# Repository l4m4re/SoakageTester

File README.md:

# SoakageTester
Hard and software for studying dielectric absorption aka "soakage" in electrolytic capacitors and/or batteries

# Intro

This is a capacitor/battery pulsed charge-discharge cycle tester, as part of a
project to investigate the theory that the well known "capacitor soakage" or
"battery action" effect observed with electrolytic capacitors can be enhanced
using pulsed charging, as demonstrated by John Bedini et al for years. For
more information on the theory, see my article about [The Cole-Hackenberger
(Gray) Power
Supply](http://www.tuks.nl/wiki/index.php/Main/ColeHackenbergerPowerSupply).

# Hardware

The hardware consists of:

1) An adjustable power supply, 0-300V;
2) Pulse charge circuitry, steered by a BeagleBone, using a MOSFET;
3) Current measurement circuitry, using a shunt, some opamps to amplify
the input signal, implement a low pass filter, etc.
4) Voltage measurement circuitry.

Both the current en voltage measurements are done by the BeagleBone using
it's analog inputs and it's ADC. 

Based on [small-scope](https://hackaday.io/project/5881-small-scope) by Marvin Sinister.

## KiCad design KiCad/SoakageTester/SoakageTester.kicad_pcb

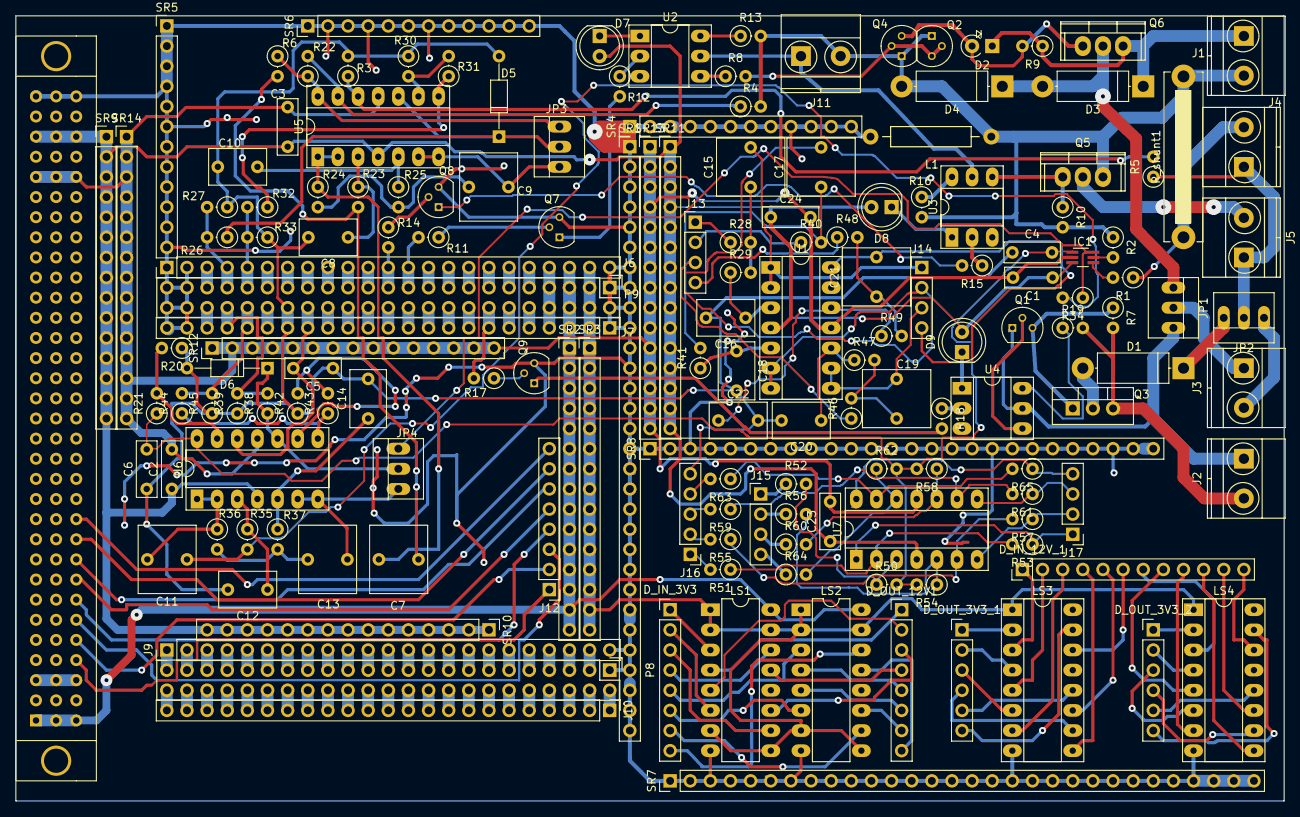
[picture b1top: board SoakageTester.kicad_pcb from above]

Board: 2 copper layers, 160.0 x 99.1 mm, 163 parts (0 on the bottom side), 230 nets.

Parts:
C1, C2, C3, C4, C5, C6, C23, C24: 100n; C_Rect_L7.0mm_W2.5mm_P5.00mm
C7, C9, C11, C13, C15, C17, C19, C21: 10n; C_Rect_L7.2mm_W8.5mm_P5.00mm_FKP2_FKP2_MKS2_MKP2
C8, C10, C12, C14, C16, C18, C20, C22: 1n; C_Rect_L7.2mm_W4.5mm_P5.00mm_FKS2_FKP2_MKS2_MKP2
D1, D3, D4: 1N4007; D_5W_P12.70mm_Horizontal
D2: 12V; D_A-405_P2.54mm_Vertical_KathodeUp
D5, D6: 1n4148; D_DO-35_SOD27_P10.16mm_Horizontal
D7, D8, D9: LED; LED_D5.0mm
D_IN_3V3: CONN_01X08; Pin_Header_Straight_1x08_Pitch2.54mm
D_IN_12V_1: CONN_01X12; Pin_Header_Straight_1x12_Pitch2.54mm
D_OUT_3V3_1, D_OUT_3V3_2: CONN_01X06; Pin_Header_Straight_1x06_Pitch2.54mm
D_OUT_12V1: CONN_01X08; Pin_Header_Straight_1x08_Pitch2.54mm
IC1: ina213; SOT-363_SC-70-6_Handsoldering
J1: 30-300V; TerminalBlock_Pheonix_MKDS1.5-2pol
J2: 12V_Bedini; TerminalBlock_Pheonix_MKDS1.5-2pol
J3: Coil; TerminalBlock_Pheonix_MKDS1.5-2pol
J4: Test Cap; TerminalBlock_Pheonix_MKDS1.5-2pol
J5: Load; TerminalBlock_Pheonix_MKDS1.5-2pol
J6, J7, J9, J10: CONN_01X23; Pin_Header_Straight_1x23_Pitch2.54mm
J8: C96ABC; C96ABCMD
J11: 12V Opto; TerminalBlock_Pheonix_MKDS1.5-2pol
J12: CONN_01X08; Pin_Header_Straight_1x08_Pitch2.54mm
J13, J14, J15, J17: CONN_01X04; Pin_Header_Straight_1x04_Pitch2.54mm
J16: CONN_01X05; Pin_Header_Straight_1x05_Pitch2.54mm
JP1, JP2, JP3, JP4: Jumper_NC_Dual; PINHEAD1-3
L1: 10m; Choke_Horizontal_RM15mm
LS1, LS2: CD40109BPW_SOP65P640X120-16N; DIP-16_W7.62mm_LongPads
LS3, LS4: CD74HC4050E_DIP254P762X508-16; DIP-16_W7.62mm_Socket_LongPads
P8, P9: BeagleBone_Black_Header; Socket_BeagleBone_Black
Q1, Q7, Q8, Q9: BC337-40; TO-92_Molded_Narrow
Q2, Q4: MPSA42; TO-92_Molded_Narrow
Q3: BUX85; TO-220_Vertical
Q5: IRFB3307; TO-220
Q6: IXTP10P50P; TO-220
R1, R2: 180k; R_Axial_DIN0207_L6.3mm_D2.5mm_P2.54mm_Vertical
R3, R6, R10, R20: 10k; R_Axial_DIN0207_L6.3mm_D2.5mm_P2.54mm_Vertical
R4, R5, R13, R16, R19, R31, R43: 1M; R_Axial_DIN0207_L6.3mm_D2.5mm_P2.54mm_Vertical
R7, R12, R15, R18, R27, R33, R39, R45: 1k; R_Axial_DIN0207_L6.3mm_D2.5mm_P2.54mm_Vertical
R8: 680; R_Axial_DIN0207_L6.3mm_D2.5mm_P2.54mm_Vertical
R9: 22k; R_Axial_DIN0207_L6.3mm_D2.5mm_P2.54mm_Vertical
R11, R14, R17: 3k3; R_Axial_DIN0207_L6.3mm_D2.5mm_P2.54mm_Vertical
R21: 20k; R_Axial_DIN0207_L6.3mm_D2.5mm_P2.54mm_Vertical
R22, R28, R34, R40, R46, R48: 453; R_Axial_DIN0207_L6.3mm_D2.5mm_P2.54mm_Vertical
R23, R35: 1k78; R_Axial_DIN0207_L6.3mm_D2.5mm_P2.54mm_Vertical
R24, R36: 243; R_Axial_DIN0207_L6.3mm_D2.5mm_P2.54mm_Vertical
R25, R37: 4k32; R_Axial_DIN0207_L6.3mm_D2.5mm_P2.54mm_Vertical
R26, R32, R38, R44: 4k99; R_Axial_DIN0207_L6.3mm_D2.5mm_P2.54mm_Vertical
R29, R41, R47, R49: 1234; R_Axial_DIN0207_L6.3mm_D2.5mm_P2.54mm_Vertical
R30, R42: 40k; R_Axial_DIN0207_L6.3mm_D2.5mm_P2.54mm_Vertical
R50, R51, R52, R53, R54, R55, R56, R57, R58, R59, R60, R61, R62, R63, R64, R65: 3456; R_Axial_DIN0207_L6.3mm_D2.5mm_P2.54mm_Vertical
R_shunt1: 10m; R_Bare_Metal_Element_L21.3mm_W4.8mm_P20.30mm
SR1, SR7: CONN_01X30; Pin_Header_Straight_1x30_Pitch2.54mm
SR2, SR3, SR9, SR10, SR11, SR12, SR13, SR14: CONN_01X15; Pin_Header_Straight_1x15_Pitch2.54mm
SR4, SR5, SR6: CONN_01X12; Pin_Header_Straight_1x12_Pitch2.54mm
SR8: CONN_01X26; Pin_Header_Straight_1x26_Pitch2.54mm
U1, U5, U6, U7: LM2902N; DIP-14_W7.62mm_Socket_LongPads
U2, U3, U4: 4N25; DIP-6_W7.62mm_Socket_LongPads

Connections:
+3V3: J6.22, J7.2, LS1.1, LS1.2, LS1.7, LS1.9, LS1.15, LS2.1, LS2.2, LS2.7, LS2.9, LS2.15, LS3.1, LS4.1, P9.3, P9.4, SR3.1, SR3.2, SR3.3, SR3.4, SR3.5, SR3.6, SR3.7, SR3.8, SR3.9, SR3.10, SR3.11, SR3.12, SR3.13, SR3.14, SR3.15
+5V: J6.21, J7.3, J8.A1, J8.B1, J8.C1, LS1.16, LS2.16, P9.5, P9.6, SR2.1, SR2.2, SR2.3, SR2.4, SR2.5, SR2.6, SR2.7, SR2.8, SR2.9, SR2.10, SR2.11, SR2.12, SR2.13, SR2.14, SR2.15
+12VA: J11.1, U2.5, U3.5
-5V: J8.A3, J8.B3, J8.C3
/Analog Experimental/Amp1/V_in+: J15.1, R52.1
/Analog Experimental/Amp1/V_in-: J16.1, R51.2
/Analog Experimental/Amp1/V_out: J17.1, R53.1, U7.1
/Analog Experimental/Amp2/V_in+: J15.2, R56.1
/Analog Experimental/Amp2/V_in-: J16.2, R55.2
/Analog Experimental/Amp2/V_out: J17.2, R57.1, U7.7
/Analog Experimental/Amp3/V_in+: J15.3, R60.1
/Analog Experimental/Amp3/V_in-: J16.3, R59.2
/Analog Experimental/Amp3/V_out: J17.3, R61.1, U7.8
/Analog Experimental/Amp4/V_in+: J15.4, R64.1
/Analog Experimental/Amp4/V_in-: J16.4, R63.2
/Analog Experimental/Amp4/V_out: J17.4, R65.1, U7.14
/Analog Experimental/Filter1/V_in: J13.1, R28.1
/Analog Experimental/Filter1/V_out: C15.2, J14.1, U1.1, U1.2
/Analog Experimental/Filter2/V_in: J13.2, R40.1
/Analog Experimental/Filter2/V_out: C17.2, J14.2, U1.6, U1.7
/Analog Experimental/Filter3/V_in: J13.3, R46.1
/Analog Experimental/Filter3/V_out: C19.2, J14.3, U1.8, U1.9
/Analog Experimental/Filter4/V_in: J13.4, R48.1
/Analog Experimental/Filter4/V_out: C21.2, J14.4, U1.13, U1.14
/Analog Experimental/V_ref: C4.2, C6.2, IC1.1, R21.1, R50.2, R54.2, R58.2, R62.2, U6.14
/Beagle/AIN0: J6.4, P9.39, R26.2, R27.2
/Beagle/AIN1: J7.20, P9.40, R38.2, R39.2
/Beagle/AIN2: J6.5, P9.37, R32.2, R33.2
/Beagle/AIN3: J7.19, P9.38, R44.2, R45.2
/Beagle/AIN4: J6.7, P9.33
/Beagle/AIN5: J7.18, P9.36
/Beagle/AIN6: J6.6, P9.35
/Beagle/Bedini: J7.7, P9.14, R17.2
/Beagle/C4: J8.C4, J12.1
/Beagle/C5: J8.C5, J12.2
/Beagle/C6: J8.C6, J12.3
/Beagle/C7: J8.C7, J12.4
/Beagle/C8: J8.C8, J12.5
/Beagle/C9: J8.C9, J12.6
/Beagle/C10: J8.C10, J12.7
/Beagle/C11: J8.C11, J12.8
/Beagle/Charge: J6.13, P9.21, R11.2
/Beagle/Discharge: J6.12, P9.23, R14.2
/Beagle/GPIO_7: J7.21, P9.42
/Beagle/GPIO_20: J6.3, P9.41
/Beagle/PWR_BUT: J6.19, P9.9
/Beagle/SYS_RESETN: J7.5, P9.10
/Input Amplifier/IC1_IN_NEG: IC1.5, R2.2
/Input Amplifier/IC1_IN_POS: IC1.4, R1.2
/Input Amplifier/I_sense: J4.2, R1.1, R_shunt1.1
/Input Amplifier/Is_x_5: IC1.6, JP4.3, R34.1
/Input Amplifier/V_cap: J4.1, J5.1, JP2.2, R5.1
/Input Amplifier/V_cap_div_100: JP3.3, R6.1, R22.1, U5.14
/Power Electronics/+300V_PWR: D2.1, D3.1, J1.1, Q6.3, R9.1
/Power Electronics/Bedini+12V: J2.1, JP1.3, Q1.1, U4.5
/Power Electronics/BediniOpto/OUT_Emitter: Q1.2, U4.4
/Power Electronics/Bedini_GND: J2.2, Q3.3, R7.2, R19.2
/Power Electronics/ChargeOpto/OUT_Emitter: R8.1, U2.4
/Power Electronics/DischargeOpto/OUT_Emitter: Q5.1, R10.1, U3.4
/experimental/1A1: D_IN_12V_1.1, LS3.3
/experimental/1A2: D_IN_12V_1.2, LS3.5
/experimental/1A3: D_IN_12V_1.3, LS3.7
/experimental/1A4: D_IN_12V_1.4, LS3.9
/experimental/1A5: D_IN_12V_1.5, LS3.11
/experimental/1A6: D_IN_12V_1.6, LS3.14
/experimental/2A1: D_IN_12V_1.7, LS4.3
/experimental/2A2: D_IN_12V_1.8, LS4.5
/experimental/2A3: D_IN_12V_1.9, LS4.7
/experimental/2A4: D_IN_12V_1.10, LS4.9
/experimental/2A5: D_IN_12V_1.11, LS4.11
/experimental/2A6: D_IN_12V_1.12, LS4.14
/experimental/A1: D_IN_3V3.1, LS1.3
/experimental/A2: D_IN_3V3.5, LS2.3
/experimental/B1: D_IN_3V3.2, LS1.6
/experimental/B2: D_IN_3V3.6, LS2.6
/experimental/C1: D_IN_3V3.3, LS1.10
/experimental/C2: D_IN_3V3.7, LS2.10
/experimental/D1: D_IN_3V3.4, LS1.14
/experimental/D2: D_IN_3V3.8, LS2.14
/experimental/E1: D_OUT_12V1.1, LS1.4
/experimental/E2: D_OUT_12V1.5, LS2.4
/experimental/F1: D_OUT_12V1.2, LS1.5
/experimental/F2: D_OUT_12V1.6, LS2.5
/experimental/G1: D_OUT_12V1.3, LS1.11
/experimental/G2: D_OUT_12V1.7, LS2.11
/experimental/H1: D_OUT_12V1.4, LS1.13
/experimental/H2: D_OUT_12V1.8, LS2.13
GNDA_ADC: C4.1, C5.1, C6.1, C8.2, C10.2, C12.2, C14.2, C16.2, C18.2, C20.2, C22.2, D5.2, D6.2, J7.17, J16.5, P9.34, R3.2, R20.1, R27.1, R30.1, R33.1, R39.1, R42.1, R45.1
GNDD: J6.1, J6.2, J6.23, J7.1, J7.22, J7.23, J8.A32, J8.B32, J8.C32, J9.23, L1.2, LS1.8, LS2.8, LS3.8, LS4.8, P8.1, P9.1, P9.2, P9.43, P9.44, P9.45, P9.46, Q7.3, Q8.3, Q9.3, SR1.1, SR1.2, SR1.3, SR1.4, SR1.5, SR1.6, SR1.7, SR1.8, SR1.9, SR1.10, SR1.11, SR1.12, SR1.13, SR1.14, SR1.15, SR1.16, SR1.17, SR1.18, SR1.19, SR1.20, SR1.21, SR1.22, SR1.23, SR1.24, SR1.25, SR1.26, SR1.27, SR1.28, SR1.29, SR1.30, SR4.1, SR4.2, SR4.3, SR4.4, SR4.5, SR4.6, SR4.7, SR4.8, SR4.9, SR4.10, SR4.11, SR4.12, SR5.1, SR5.2, SR5.3, SR5.4, SR5.5, SR5.6, SR5.7, SR5.8, SR5.9, SR5.10, SR5.11, SR5.12, SR6.1, SR6.2, SR6.3, SR6.4, SR6.5, SR6.6, SR6.7, SR6.8, SR6.9, SR6.10, SR6.11, SR6.12, SR7.1, SR7.2, SR7.3, SR7.4, SR7.5, SR7.6, SR7.7, SR7.8, SR7.9, SR7.10, SR7.11, SR7.12, SR7.13, SR7.14, SR7.15, SR7.16, SR7.17, SR7.18, SR7.19, SR7.20, SR7.21, SR7.22, SR7.23, SR7.24, SR7.25, SR7.26, SR7.27, SR7.28, SR7.29, SR7.30, SR8.1, SR8.2, SR8.3, SR8.4, SR8.5, SR8.6, SR8.7, SR8.8, SR8.9, SR8.10, SR8.11, SR8.12, SR8.13, SR8.14, SR8.15, SR8.16, SR8.17, SR8.18, SR8.19, SR8.20, SR8.21, SR8.22, SR8.23, SR8.24, SR8.25, SR8.26
GNDPWR: D4.2, J1.2, J11.2, L1.1, Q2.1, Q4.1, Q5.3, R2.1, R4.2, R10.2, R13.2, R16.2, R_shunt1.2
unnamed: C7.1, R22.2, R23.2
unnamed: C7.2, R24.1, U5.1, U5.2
unnamed: C8.1, R23.1, U5.3
unnamed: C9.1, R24.2, R25.2
unnamed: C9.2, JP3.1, U5.6, U5.7
unnamed: C10.1, R25.1, U5.5
unnamed: C11.1, R34.2, R35.2
unnamed: C11.2, R36.1, U6.1, U6.2
unnamed: C12.1, R35.1, U6.3
unnamed: C13.1, R36.2, R37.2
unnamed: C13.2, JP4.1, U6.6, U6.7
unnamed: C14.1, R37.1, U6.5
unnamed: C15.1, R28.2, R29.2
unnamed: C16.1, R29.1, U1.3
unnamed: C17.1, R40.2, R41.2
unnamed: C18.1, R41.1, U1.5
unnamed: C19.1, R46.2, R47.2
unnamed: C20.1, R47.1, U1.10
unnamed: C21.1, R48.2, R49.2
unnamed: C22.1, R49.1, U1.12
unnamed: D1.1, JP2.3
unnamed: D1.2, Q3.2
unnamed: D2.2, Q4.3, Q6.1, R9.2
unnamed: D3.2, D4.1, JP1.1, Q6.2
unnamed: D5.1, JP3.2, R26.1, U5.10
unnamed: D6.1, JP4.2, R38.1, U6.10
unnamed: D7.1, U2.1
unnamed: D8.1, U3.1
unnamed: D9.1, U4.1
unnamed: D_OUT_3V3_1.1, LS3.2
unnamed: D_OUT_3V3_1.2, LS3.4
unnamed: D_OUT_3V3_1.3, LS3.6
unnamed: D_OUT_3V3_1.4, LS3.10
unnamed: D_OUT_3V3_1.5, LS3.12
unnamed: D_OUT_3V3_1.6, LS3.15
unnamed: D_OUT_3V3_2.1, LS4.2
unnamed: D_OUT_3V3_2.2, LS4.4
unnamed: D_OUT_3V3_2.3, LS4.6
unnamed: D_OUT_3V3_2.4, LS4.10
unnamed: D_OUT_3V3_2.5, LS4.12
unnamed: D_OUT_3V3_2.6, LS4.15
unnamed: J3.1, JP1.2
unnamed: J3.2, JP2.1
unnamed: J5.2, Q5.2
unnamed: J6.8, P9.31
unnamed: J6.9, P9.29
unnamed: J6.10, P9.27
unnamed: J6.11, P9.25
unnamed: J6.14, P9.19
unnamed: J6.15, P9.17
unnamed: J6.16, P9.15
unnamed: J6.17, P9.13
unnamed: J6.18, P9.11
unnamed: J7.6, P9.12
unnamed: J7.8, P9.16
unnamed: J7.9, P9.18
unnamed: J7.10, P9.20
unnamed: J7.11, P9.22
unnamed: J7.12, P9.24
unnamed: J7.13, P9.26
unnamed: J7.14, P9.28
unnamed: J7.15, P9.30
unnamed: J9.1, P8.45
unnamed: J9.2, P8.43
unnamed: J9.3, P8.41
unnamed: J9.4, P8.39
unnamed: J9.5, P8.37
unnamed: J9.6, P8.35
unnamed: J9.7, P8.33
unnamed: J9.8, P8.31
unnamed: J9.9, P8.29
unnamed: J9.10, P8.27
unnamed: J9.11, P8.25
unnamed: J9.12, P8.23
unnamed: J9.13, P8.21
unnamed: J9.14, P8.19
unnamed: J9.15, P8.17
unnamed: J9.16, P8.15
unnamed: J9.17, P8.13
unnamed: J9.18, P8.11
unnamed: J9.19, P8.9
unnamed: J9.20, P8.7
unnamed: J9.21, P8.5
unnamed: J9.22, P8.3
unnamed: J10.1, P8.2
unnamed: J10.2, P8.4
unnamed: J10.3, P8.6
unnamed: J10.4, P8.8
unnamed: J10.5, P8.10
unnamed: J10.6, P8.12
unnamed: J10.7, P8.14
unnamed: J10.8, P8.16
unnamed: J10.9, P8.18
unnamed: J10.10, P8.20
unnamed: J10.11, P8.22
unnamed: J10.12, P8.24
unnamed: J10.13, P8.26
unnamed: J10.14, P8.28
unnamed: J10.15, P8.30
unnamed: J10.16, P8.32
unnamed: J10.17, P8.34
unnamed: J10.18, P8.36
unnamed: J10.19, P8.38
unnamed: J10.20, P8.40
unnamed: J10.21, P8.42
unnamed: J10.22, P8.44
unnamed: J10.23, P8.46
unnamed: Q1.3, Q3.1, R7.1
unnamed: Q2.2, Q2.3, Q4.2, R8.2
unnamed: Q7.1, R12.2
unnamed: Q7.2, R11.1
unnamed: Q8.1, R15.2
unnamed: Q8.2, R14.1
unnamed: Q9.1, R18.2
unnamed: Q9.2, R17.1
unnamed: R3.1, R5.2, U5.12
unnamed: R4.1, R6.2, U5.13
unnamed: R12.1, U2.2
unnamed: R13.1, U2.6
unnamed: R15.1, U3.2
unnamed: R16.1, U3.6
unnamed: R18.1, U4.2
unnamed: R19.1, U4.6
unnamed: R20.2, R21.2, U6.13
unnamed: R30.2, R31.2, U5.9
unnamed: R31.1, R32.1, U5.8
unnamed: R42.2, R43.2, U6.9
unnamed: R43.1, R44.1, U6.8
unnamed: R50.1, R52.2, U7.3
unnamed: R51.1, R53.2, U7.2
unnamed: R54.1, R56.2, U7.5
unnamed: R55.1, R57.2, U7.6
unnamed: R58.1, R60.2, U7.10
unnamed: R59.1, R61.2, U7.9
unnamed: R62.1, R64.2, U7.12
unnamed: R63.1, R65.2, U7.13
OPAMP_Vdd: C1.2, C2.2, C3.2, C23.2, C24.2, IC1.2, J8.A28, J8.B28, J8.C28, SR12.1, SR12.2, SR12.3, SR12.4, SR12.5, SR12.6, SR12.7, SR12.8, SR12.9, SR12.10, SR12.11, SR12.12, SR12.13, SR12.14, SR12.15, SR13.1, SR13.2, SR13.3, SR13.4, SR13.5, SR13.6, SR13.7, SR13.8, SR13.9, SR13.10, SR13.11, SR13.12, SR13.13, SR13.14, SR13.15, SR14.1, SR14.2, SR14.3, SR14.4, SR14.5, SR14.6, SR14.7, SR14.8, SR14.9, SR14.10, SR14.11, SR14.12, SR14.13, SR14.14, SR14.15, U1.11, U5.11, U6.11, U7.11
OPAMP_Vss: C1.1, C2.1, C3.1, C23.1, C24.1, D7.2, D8.2, D9.2, IC1.3, J8.A30, J8.B30, J8.C30, SR9.1, SR9.2, SR9.3, SR9.4, SR9.5, SR9.6, SR9.7, SR9.8, SR9.9, SR9.10, SR9.11, SR9.12, SR9.13, SR9.14, SR9.15, SR10.1, SR10.2, SR10.3, SR10.4, SR10.5, SR10.6, SR10.7, SR10.8, SR10.9, SR10.10, SR10.11, SR10.12, SR10.13, SR10.14, SR10.15, SR11.1, SR11.2, SR11.3, SR11.4, SR11.5, SR11.6, SR11.7, SR11.8, SR11.9, SR11.10, SR11.11, SR11.12, SR11.13, SR11.14, SR11.15, U1.4, U5.4, U6.4, U7.4
SYS_5V: J6.20, J7.4, P9.7, P9.8
VDD_ADC: C5.2, J7.16, P9.32, U6.12

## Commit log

2015-03-02 Added (source) files from old Arduino project.
2017-07-09 Check-in of PCB files.
2017-07-09 Added errata file with known issues.
2017-07-09 removed eagle format library; added licensing info
2017-09-03 Imported some components to LamaresLib.
2017-09-03 Basic components working.
2017-09-04 First, rudimentary working code and setup.
2017-09-07 More or less working, but sampling stops while operating GPIO
2017-09-11 A step further. Works reasonably, but cleanup to do.
2017-09-11 Reverted workaround for perceived GPIO interference with sampler.
2017-09-17 Added zener to lamareslib.
2017-09-17 Added coil to Lamareslib.
2017-09-18 Copied Kicad schematic to version 2.
2017-09-21 Included digital BiQuad low pass filter.
2017-09-22 Clean up and replace libpruio with dedicated pru program.
2017-09-22 Implemented 200 kHz low pass, 8th order Butterworth filter.
2017-09-28 Changed to Bedini charge mode
2017-09-30 Change to Bedini mode. Keep samling thread alive after error.
2017-10-02 We were missing samples. Changed to ring buffer and RT priority thread.
2017-10-03 Fixed Pru c-compiler directories, so the proper files are included.
2018-05-19 Added reference to background article.
